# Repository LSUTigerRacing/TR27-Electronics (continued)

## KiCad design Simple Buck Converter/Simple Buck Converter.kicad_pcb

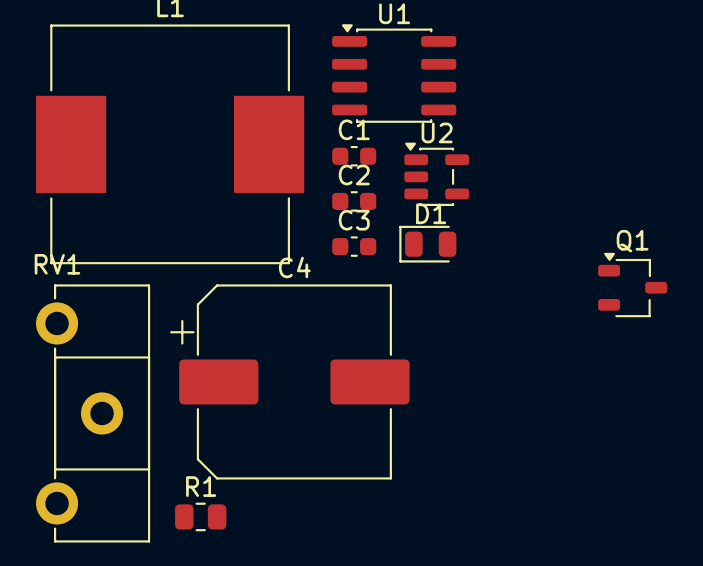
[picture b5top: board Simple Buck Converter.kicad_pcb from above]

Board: 2 copper layers, 11 parts (0 on the bottom side), 8 nets, no tracks yet.

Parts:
C1: 30nF; C_0603_1608Metric
C2, C3: 100nF; C_0603_1608Metric
C4: 100uF; CP_Elec_10x10.5
D1: D; D_0805_2012Metric
L1: 1H; L_Neosid_SM-NE127_HandSoldering
Q1: Q_NMOS; TSOT-23
R1: 10k; R_0805_2012Metric
RV1: 10k; Potentiometer_ACP_CA14-H2,5_Horizontal
U1: LM555xM; SOIC-8_3.9x4.9mm_P1.27mm
U2: LM397; SOT-23-5

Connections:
+12V: C2.1, C3.1, RV1.1, U1.4 (~RST), U1.8 (VCC), U2.5 (V+)
/555Out: R1.2, U1.3 (OUT), U2.3 (+)
/Converter+: C4.1, L1.2
GND: C1.2, C2.2, C3.2, C4.2, D1.2 (A), RV1.3, U1.1 (GND), U2.2 (V-)
unnamed: D1.1 (K), L1.1
unnamed: R1.1, U1.7 (DISCH)
unnamed: C1.1, U1.2 (TRIG), U1.6 (THRES)
unnamed: RV1.2, U2.1 (-)

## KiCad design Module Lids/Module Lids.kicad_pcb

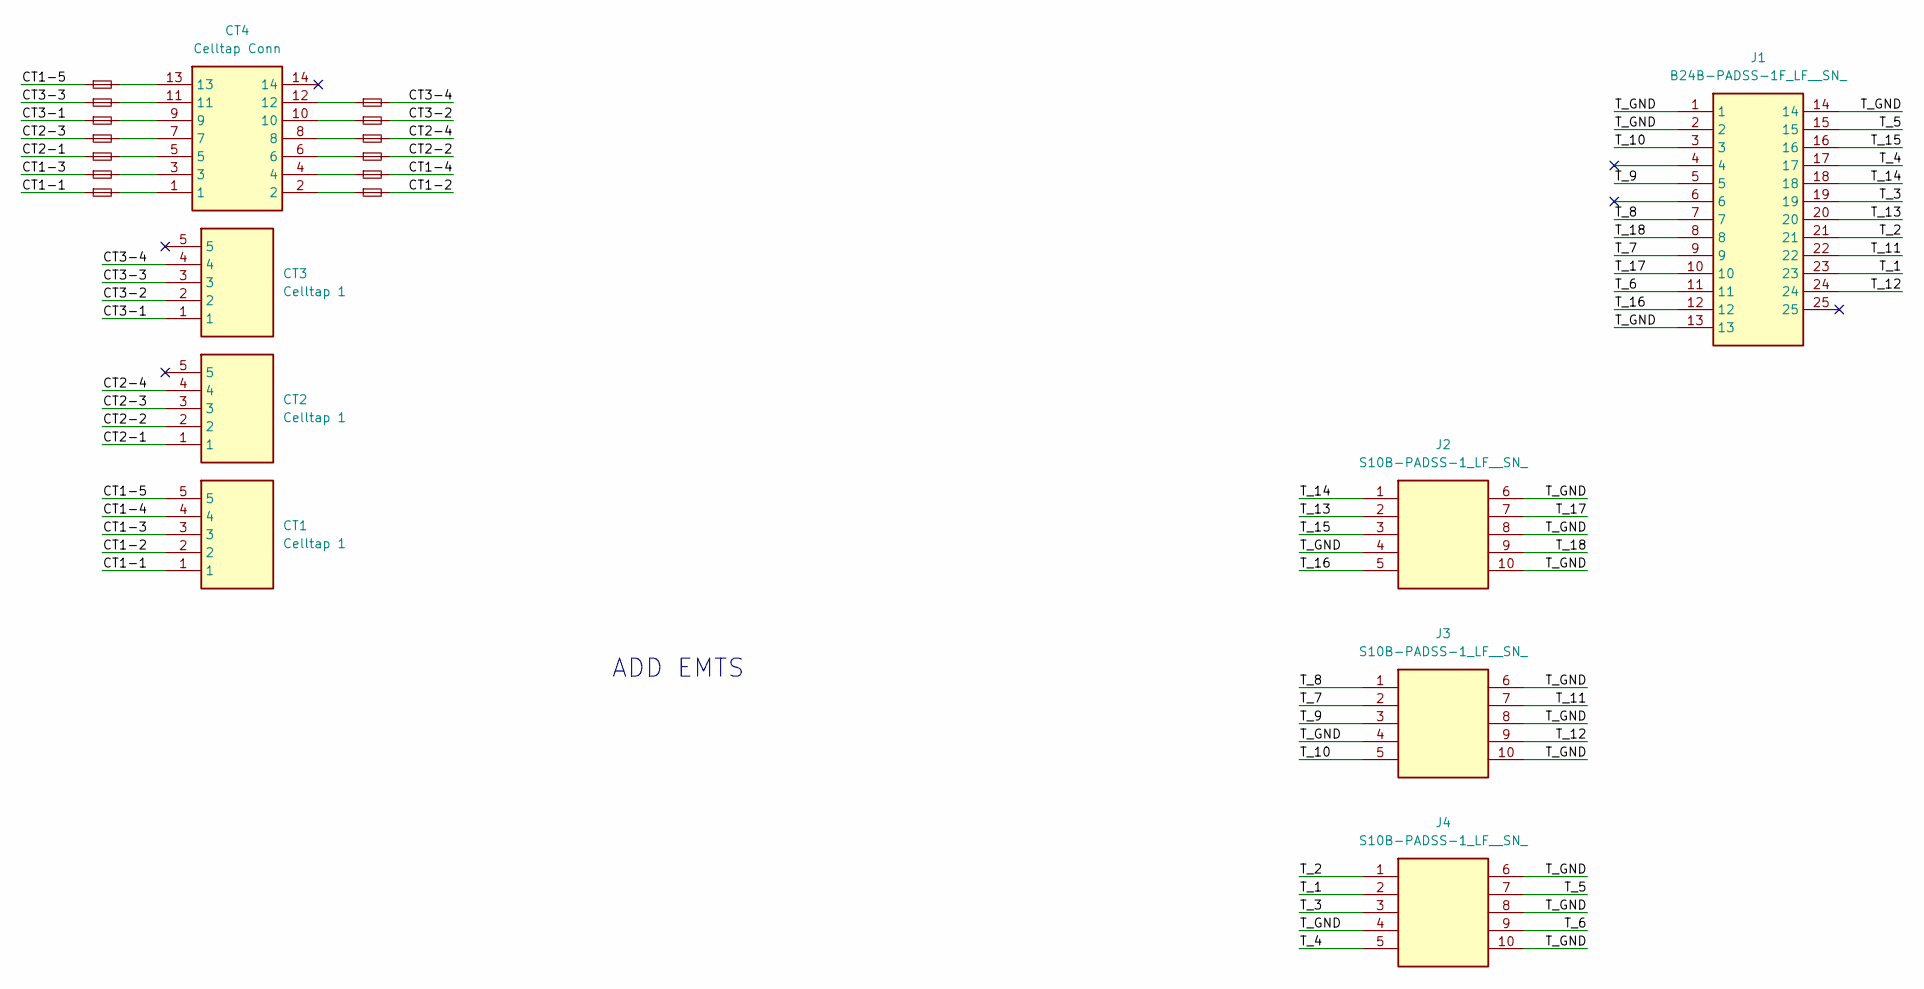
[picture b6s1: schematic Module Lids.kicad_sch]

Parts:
CT1, CT2, CT3: Celltap 1; 5-Pin-Molex; Mouser Part Number 538-215760-1005
CT4: Celltap Conn; 14-Pin-Molex; Mouser Part Number 538-206832-1401
F1, F2, F3, F4, F5, F6, F7, F8, F9, F10, F11, F12, F13: Fuse_Small; Fuse_1206_3216Metric_Pad1.42x1.75mm_HandSolder
J1: B24B-PADSS-1F_LF__SN_; 24-Pin-JST; Mouser Part Number 306-B24BPADSS1FLFSN
J2, J3, J4: S10B-PADSS-1_LF__SN_; 10-Pin-JST; Mouser Part Number 306-S10BPADSS1LFSN

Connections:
/CT1-1: CT1.1, F1.1
/CT1-2: CT1.2, F2.2
/CT1-3: CT1.3, F3.1
/CT1-4: CT1.4, F4.2
/CT1-5: CT1.5, F13.1
/CT2-1: CT2.1, F5.1
/CT2-2: CT2.2, F6.2
/CT2-3: CT2.3, F7.1
/CT2-4: CT2.4, F8.2
/CT3-1: CT3.1, F9.1
/CT3-2: CT3.2, F10.2
/CT3-3: CT3.3, F11.1
/CT3-4: CT3.4, F12.2
/T_1: J1.23, J4.2
/T_2: J1.21, J4.1
/T_3: J1.19, J4.3
/T_4: J1.17, J4.5
/T_5: J1.15, J4.7
/T_6: J1.11, J4.9
/T_7: J1.9, J3.2
/T_8: J1.7, J3.1
/T_9: J1.5, J3.3
/T_10: J1.3, J3.5
/T_11: J1.22, J3.7
/T_12: J1.24, J3.9
/T_13: J1.20, J2.2
/T_14: J1.18, J2.1
/T_15: J1.16, J2.3
/T_16: J1.12, J2.5
/T_17: J1.10, J2.7
/T_18: J1.8, J2.9
/T_GND: J1.1, J1.2, J1.13, J1.14, J2.4, J2.6, J2.8, J2.10, J3.4, J3.6, J3.8, J3.10, J4.4, J4.6, J4.8, J4.10
unnamed: CT4.1, F1.2
unnamed: CT4.2, F2.1
unnamed: CT4.3, F3.2
unnamed: CT4.4, F4.1
unnamed: CT4.5, F5.2
unnamed: CT4.6, F6.1
unnamed: CT4.7, F7.2
unnamed: CT4.8, F8.1
unnamed: CT4.9, F9.2
unnamed: CT4.10, F10.1
unnamed: CT4.11, F11.2
unnamed: CT4.12, F12.1
unnamed: CT4.13, F13.2

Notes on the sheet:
ADD EMTS

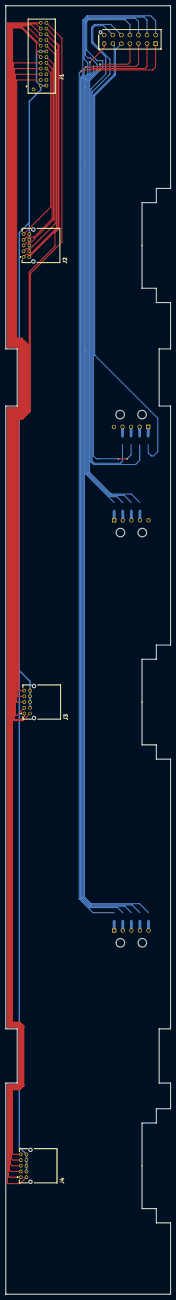
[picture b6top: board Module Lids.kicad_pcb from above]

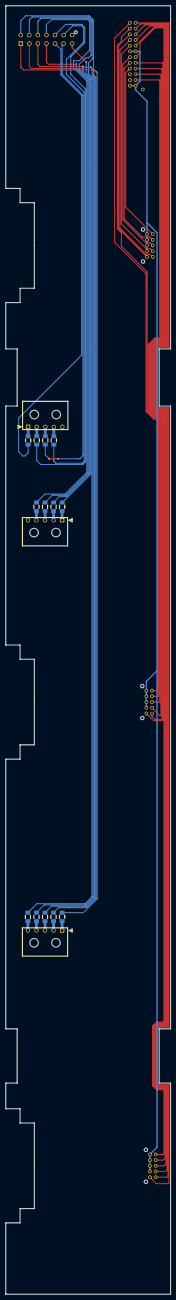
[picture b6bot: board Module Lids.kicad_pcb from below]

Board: 2 copper layers, 57.8 x 451.5 mm, 21 parts (16 on the bottom side), 45 nets.

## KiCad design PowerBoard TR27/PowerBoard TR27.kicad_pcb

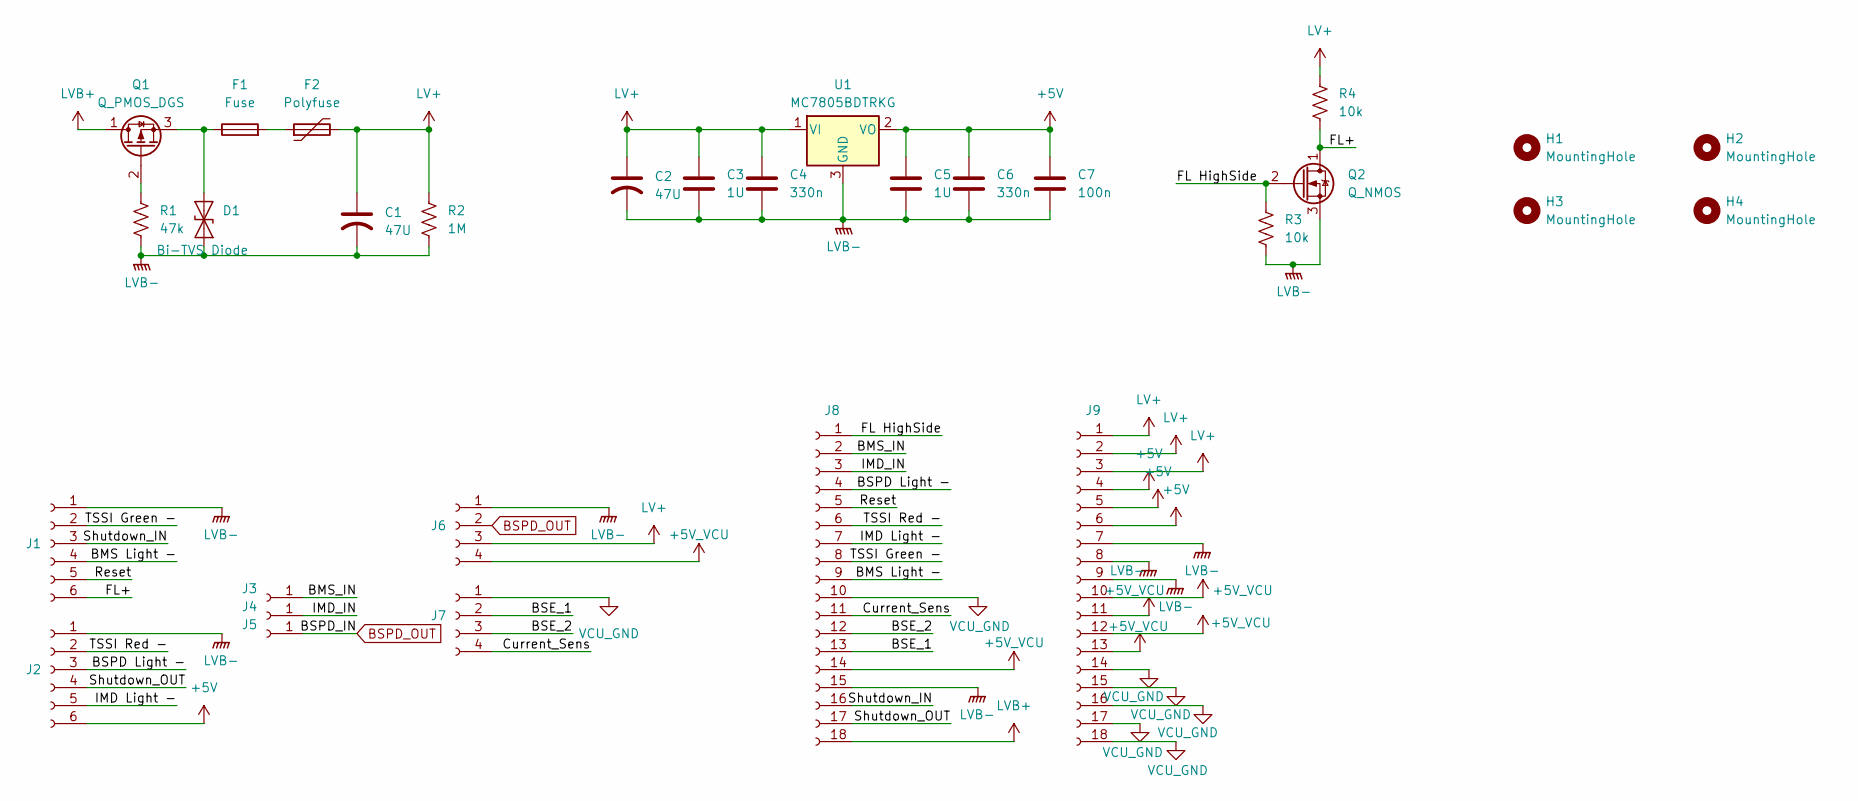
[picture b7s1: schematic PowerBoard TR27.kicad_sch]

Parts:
C1, C2: 47U; CP_Elec_6.3x5.4; JLC# C2836440
C3, C5: 1U; C_0603_1608Metric
C4, C6: 330n; C_0603_1608Metric
C7: 100n; C_0603_1608Metric
D1: Bi-TVS Diode; D_SOD-523; Mouser# 750-CPDUR12V-HF; JLC# C2443698
F1: Fuse; Fuseholder_Blade_Mini_Keystone_3568
F2: Polyfuse; R_0805_2012Metric
H1, H2, H3, H4: MountingHole; MountingHole_3.2mm_M3_DIN965_Pad
J1, J2: Conn_01x06_Socket; SAMTEC-CES-103-01-X-D
J3, J4, J5: Conn_01x01_Socket; SAMTEC_CES-101-01-T-S
J6, J7: Conn_01x04_Socket; SAMTEC_CES-104-X-X-S
J8, J9: Conn_01x18_Socket; CONN_SD-43045-001_18_MOL
Q1: Q_PMOS_DGS; SOT-23-3
Q2: Q_NMOS; SOT-23-3
R1: 47k; R_0805_2012Metric
R2: 1M; R_0805_2012Metric
R3, R4: 10k; R_0805_2012Metric
U1: MC7805BDTRKG; TO-252-3_TabPin2

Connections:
+5V: C5.1, C6.1, C7.1, J2.6, J9.4, J9.5, J9.6, U1.2 (VO)
+5V_VCU: J6.4, J8.14, J9.10, J9.11, J9.12, J9.13
/BMS Light -: J1.4, J8.9
/BMS_IN: J3.1 (Pin_1_1), J8.2
/BSE_1: J7.2, J8.13
/BSE_2: J7.3, J8.12
/BSPD Light -: J2.3, J8.4
/Current_Sens: J7.4, J8.11
/FL HighSide: J8.1, Q2.2 (G), R3.1
/FL+: J1.6, Q2.1 (D), R4.2
/IMD Light -: J2.5, J8.7
/IMD_IN: J4.1 (Pin_1_1), J8.3
/Reset: J1.5, J8.5
/Shutdown_IN: J1.3, J8.16
/Shutdown_OUT: J2.4, J8.17
/TSSI Green -: J1.2, J8.8
/TSSI Red -: J2.2, J8.6
BSPD_OUT: J5.1 (Pin_1_1), J6.2
LV+: C1.1, C2.1, C3.1, C4.1, F2.2, J6.3, J9.1, J9.2, J9.3, R2.1, R4.1, U1.1 (VI)
LVB+: J8.18, Q1.1 (D)
LVB-: C1.2, C2.2, C3.2, C4.2, C5.2, C6.2, C7.2, D1.1 (A1), J1.1, J2.1, J6.1, J8.15, J9.7, J9.8, J9.9, Q2.3 (S), R1.2, R2.2, R3.2, U1.3 (GND)
unnamed: D1.2 (A2), F1.1, Q1.3 (S)
unnamed: F1.2, F2.1
unnamed: Q1.2 (G), R1.1
VCU_GND: J7.1, J8.10, J9.14, J9.15, J9.16, J9.17, J9.18

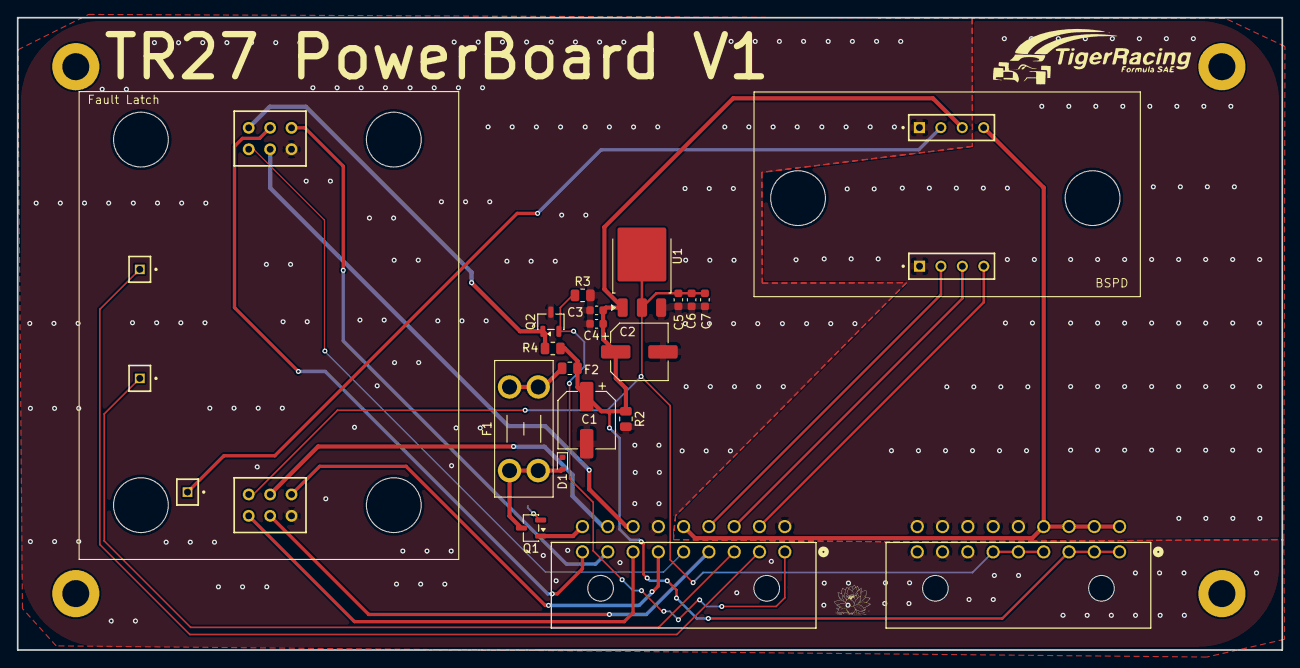
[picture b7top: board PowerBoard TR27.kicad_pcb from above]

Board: 2 copper layers, 150.0 x 75.0 mm, 30 parts (1 on the bottom side), 25 nets.

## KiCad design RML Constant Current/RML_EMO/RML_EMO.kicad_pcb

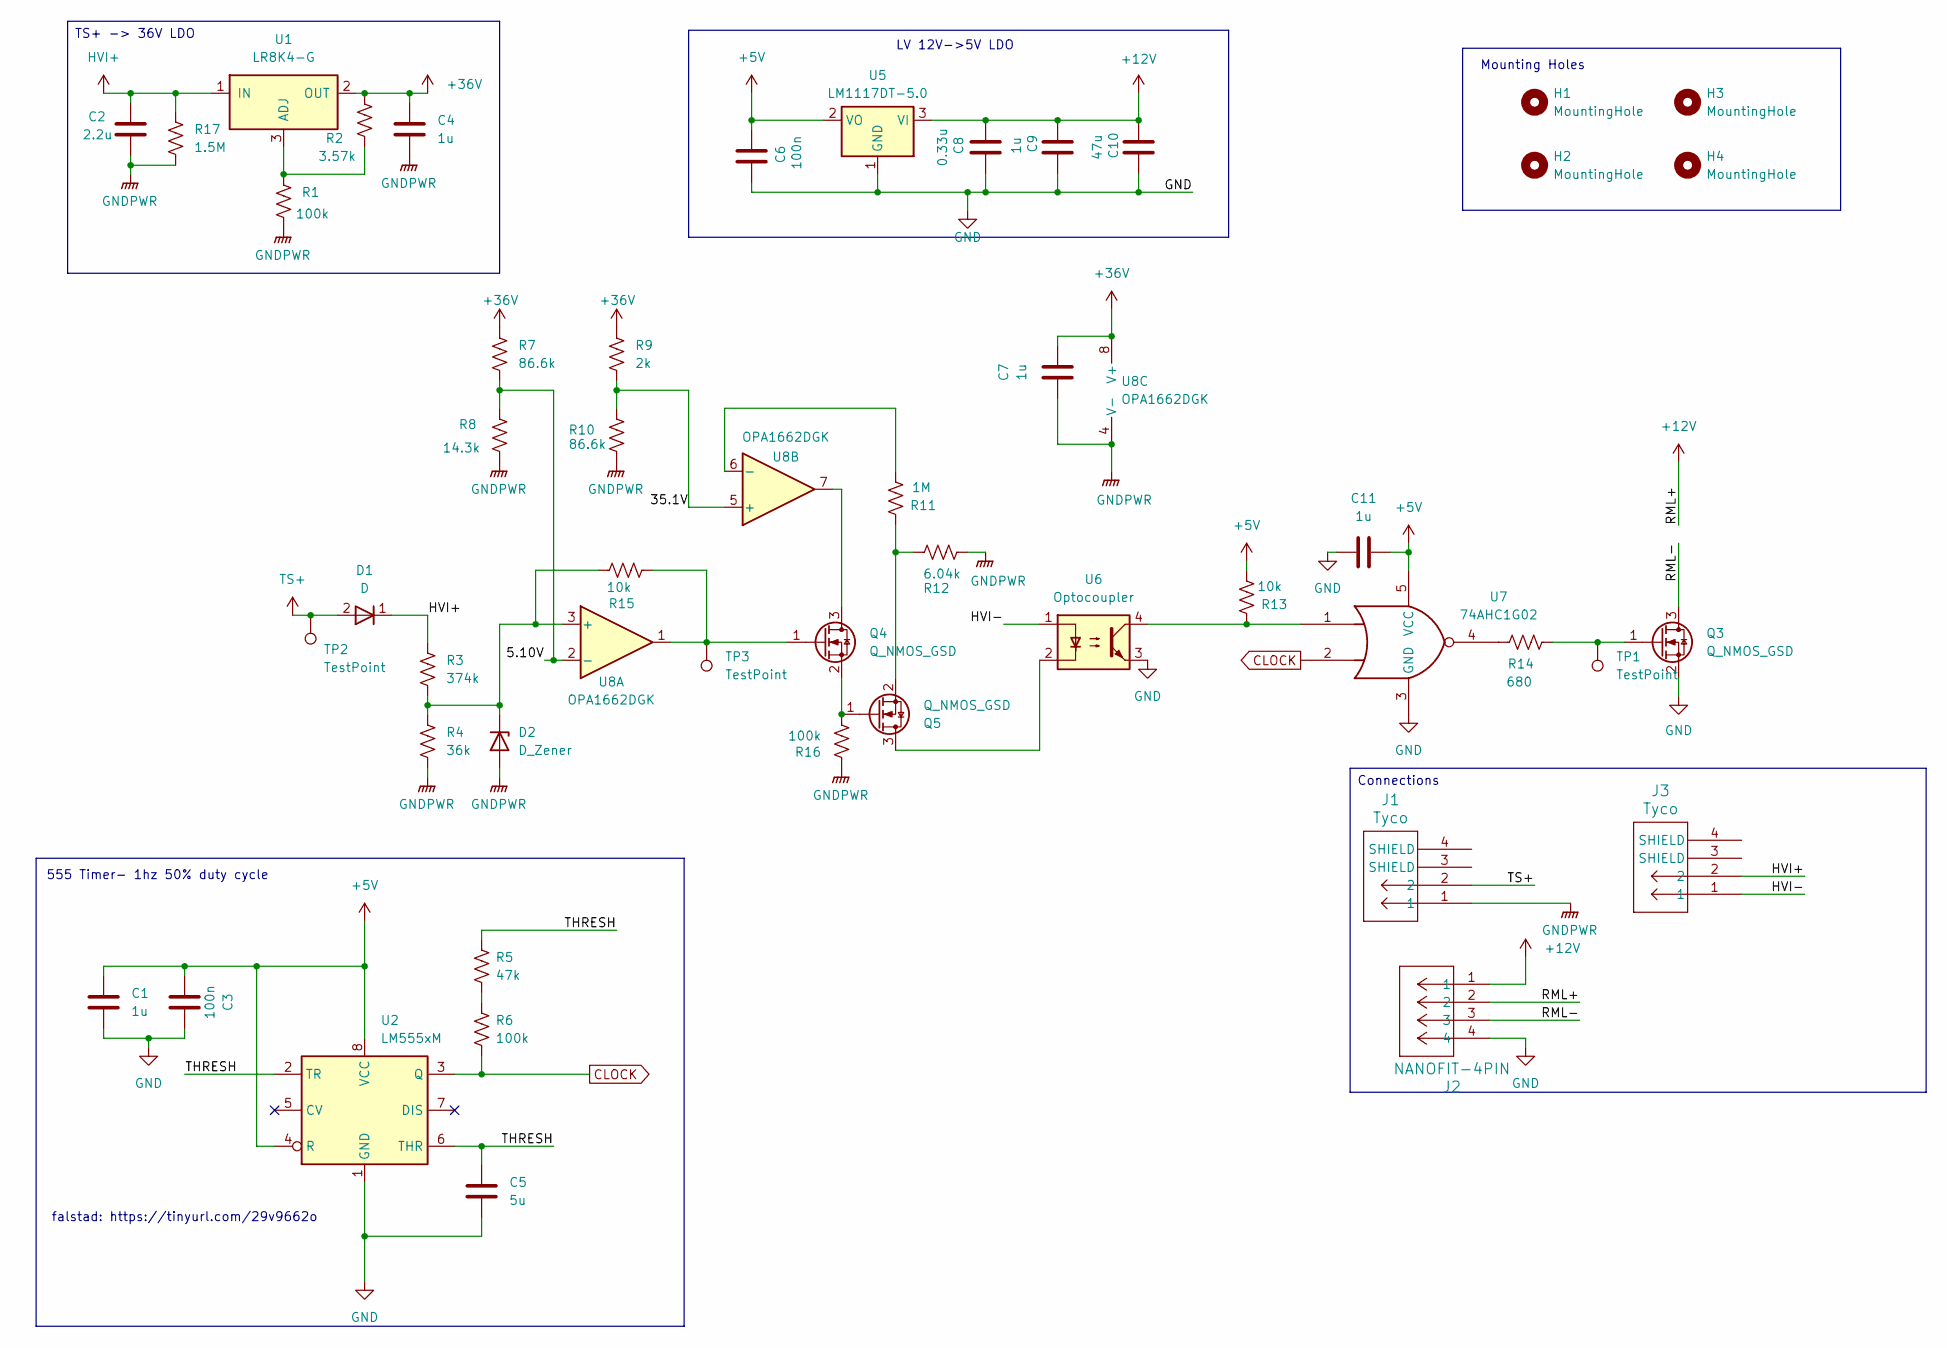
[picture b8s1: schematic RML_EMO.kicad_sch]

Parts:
C1: 1u; C_0603_1608Metric; Mouser# 603-AC0805KKX7R9B105
C2: 2.2u; CAP_6050_TDK; Manufacturer# CAA572X6T2W225M640LJ; Digikey# 445-CAA572X6T2W225M640LJCT-ND
C3: 100n; C_0603_1608Metric; Mouser# 603-AC0603KR9BB104
C4, C7, C9, C11: 1u; C_0805_2012Metric_Pad1.18x1.45mm_HandSolder; Mouser# 603-AC0805KKX7R9B105
C5: 5u; C_0603_1608Metric; Mouser# 963-MLASG168BB5475KT
C6: 100n; C_0603_1608Metric_Pad1.08x0.95mm_HandSolder; Mouser# 603-AC0603KR9BB104
C8: 0.33u; C_0603_1608Metric_Pad1.08x0.95mm_HandSolder; Manufacturer# CC0603KRX7R6BB334; JLC# C282682
C10: 47u; CP_Elec_6.3x5.4; JLC# C2836440
D1: D; D_SOD-523; Mouser# 755-RFU01SM4ST2R
D2: D_Zener; Nexperia_CFP3_SOD-123W; Manufacturer# MMSZ5240C-HE3_A-08; Mouser# 78-MMSZ5240CHE3_A-08
H1, H2, H3, H4: MountingHole; MountingHole_3.2mm_M3_DIN965_Pad_TopOnly
J1, J3: Tyco; tyco
J2: NANOFIT-4PIN; Molex_Nano-Fit_105313-xx04_1x04_P2.50mm_Horizontal
Q3: Q_NMOS_GSD; SOT-23; JLC# C2590
Q4: Q_NMOS_GSD; SOT-23; Digikey# 5318-AM2398N-ND
Q5: Q_NMOS_GSD; TO-220-3_Vertical; Digikey# IPP60R180P7XKSA1-ND
R1, R16: 100k; R_0805_2012Metric_Pad1.20x1.40mm_HandSolder; Manufacturer# RC0805FR-10100KL; Digikey# 13-RC0805FR-10100KLCT-ND
R2: 3.57k; R_0805_2012Metric_Pad1.20x1.40mm_HandSolder; Mouser# 652-CR0805FX-3571ELF
R3: 374k; R_0805_2012Metric; Mouser# 71-CRCW0805374KFKEA
R4: 36k; R_0805_2012Metric_Pad1.20x1.40mm_HandSolder; Mouser# 667-ERJ-P06F3602V
R5: 47k; R_1206_3216Metric; Manufacturer# RC1206FR-0747KL; JLC# C25664
R6: 100k; R_1206_3216Metric; Manufacturer# RC1206FR-07100KL; JLC# C17900
R7, R10: 86.6k; R_0805_2012Metric_Pad1.20x1.40mm_HandSolder; Mouser# 667-ERJ-P06F8662V
R8: 14.3k; R_0805_2012Metric_Pad1.20x1.40mm_HandSolder; Mouser# 667-ERJ-P06F1432V
R9: 2k; R_0805_2012Metric_Pad1.20x1.40mm_HandSolder; Mouser# 71-CRCW08052K00JNEA
R11: 1M; R_0805_2012Metric_Pad1.20x1.40mm_HandSolder; Mouser# 667-ERJ-P06J105V
R12: 6.04k; R_0805_2012Metric_Pad1.20x1.40mm_HandSolder; Mouser# 667-ERJ-P06F6041V
R13, R15: 10k; R_0805_2012Metric_Pad1.20x1.40mm_HandSolder; Manufacturer# 311-10.0KCRCT-ND; Digikey# 603-RC0805FR-0710KL
R14: 680; R_0805_2012Metric_Pad1.20x1.40mm_HandSolder; Mouser# 603-RC0805FR-07680RL
R17: 1.5M; R_2010_5025Metric_Pad1.40x2.65mm_HandSolder; Mouser# 603-RC2010JK-071M5L
TP1, TP2, TP3: TestPoint; TestPoint_Pad_1.0x1.0mm
U1: LR8K4-G; TO-252-2; Manufacturer# LR8K4-G; Digikey# LR8K4-GCT-ND
U2: LM555xM; SOIC-8_3.9x4.9mm_P1.27mm; Manufacturer# LMC555CMX/NOPBCT-ND; JLC# C90760
U5: LM1117DT-5.0; TO-252-3_TabPin2; Manufacturer# LM1117DT-5.0/NOPB; JLC# C354068
U6: Optocoupler; Q_Wurth_WL-OCPT_LSOP4-STANDARD; Mouser# 78-VOLA617A-3X001T
U7: 74AHC1G02; SOT-353_SC-70-5; Mouser# 595-SN74AHC1G02DCG4
U8: OPA1662DGK; VSSOP-8_3x3mm_P0.65mm; Mouser# OPA1662DGK

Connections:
+5V: C1.1, C3.1, C6.2, C11.1, R13.1, U2.4 (R), U2.8 (VCC), U5.2 (VO), U7.5 (VCC)
+12V: C8.1, C9.1, C10.1, J2.1, J2.2, U5.3 (VI)
+36V: C4.1, C7.1, R2.2, R7.2, R9.2, U1.2 (OUT), U8.8 (V+)
/5.10V: R7.1, R8.2, U8.2 (-)
/35.1V: R9.1, R10.2, U8.5 (+)
/HVI-: J3.1, U6.1
/RML-: J2.3, Q3.3 (D)
/THRESH: C5.1, R5.1, U2.2 (TR), U2.6 (THR)
CLOCK: R6.2, U2.3 (Q), U7.2
GND: C1.2, C3.2, C5.2, C6.1, C8.2, C9.2, C10.2, C11.2, J2.4, Q3.2 (S), U2.1 (GND), U5.1 (GND), U6.3, U7.3 (GND)
GNDPWR: C2.2, C4.2, C7.2, D2.2 (A), J1.1, R1.1, R4.2, R8.1, R10.1, R12.2, R16.2, R17.1, U8.4 (V-)
HVI+: C2.1, D1.1 (K), J3.2, R3.1, R17.2, U1.1 (IN)
unnamed: D2.1 (K), R3.2, R4.1, R15.2, U8.3 (+)
unnamed: Q3.1 (G), R14.1, TP1.1 (1_1)
unnamed: Q4.3 (D), U8.7
unnamed: Q4.1 (G), R15.1, TP3.1 (1_1), U8.1
unnamed: Q4.2 (S), Q5.1 (G), R16.1
unnamed: Q5.3 (D), U6.2
unnamed: Q5.2 (S), R11.2, R12.1
unnamed: R5.2, R6.1
unnamed: R13.2, U6.4, U7.1
unnamed: R14.2, U7.4
unnamed: R1.2, R2.1, U1.3 (ADJ)
unnamed: R11.1, U8.6 (-)
TS+: D1.2 (A), J1.2, TP2.1 (1_1)

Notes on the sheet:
Mounting Holes
555 Timer- 1hz 50% duty cycle
LV 12V->5V LDO
falstad: https://tinyurl.com/29v9662o
TS+ -> 36V LDO
Connections

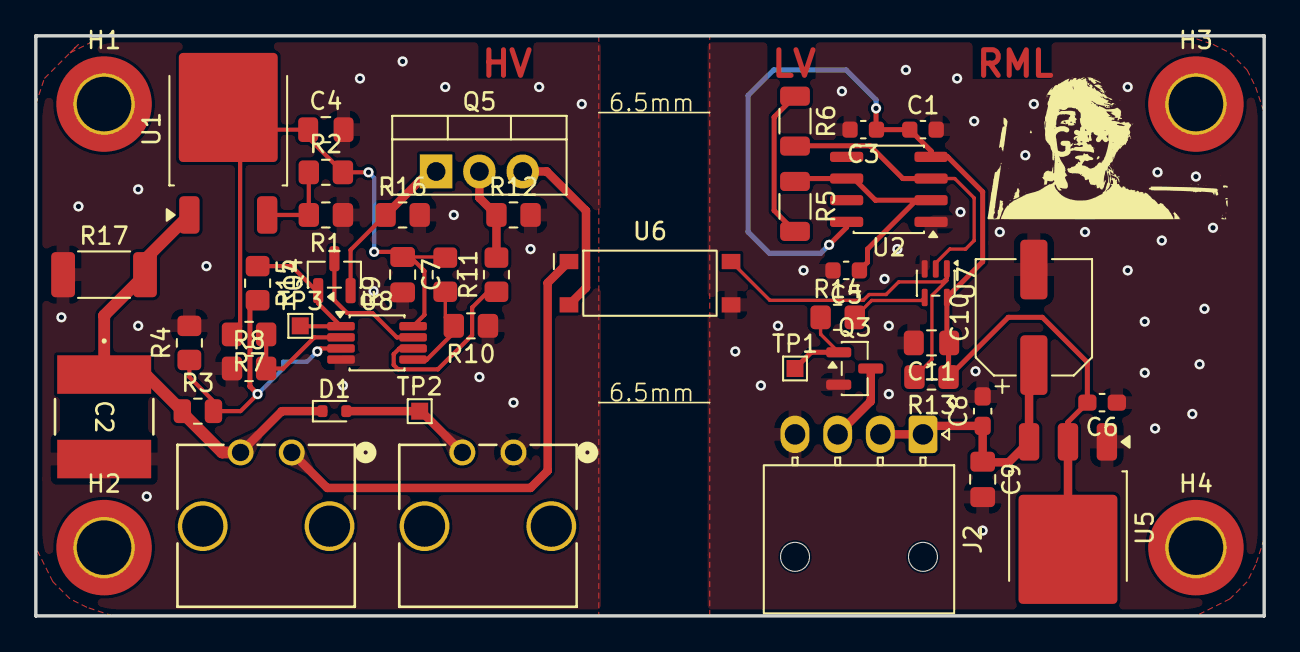
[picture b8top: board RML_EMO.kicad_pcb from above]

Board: 2 copper layers, 72.0 x 34.0 mm, 49 parts (1 on the bottom side), 25 nets.
